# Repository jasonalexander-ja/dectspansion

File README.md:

# DECTspansion 

A DECT module for your EMFCamp Tildagon badge. 

Requires a headphone input. 

Based on [sc14cvmdect-devboard](https://github.com/funkeleinhorn/sc14cvmdect-devboard) by [funkeleinhorn](https://github.com/funkeleinhorn) and [EMFCamp](https://www.emfcamp.org/) [hexpansion](https://github.com/emfcamp/badge-2024-hardware/tree/main/hexpansion). 

Currently in early prototype stage. 

## Components 

| Component | Value          | Footprint      |
|-----------|----------------|----------------|
| C1        | 47pF           | 0603           |
| C2        | 2.2uF          | 0805           |
| C3        | 10uF           | 0805           |
| C4        | 2.2uF          | 0805           |
| C5        | 100nF          | 0603           |
| C6        | 1nF            | 0603           |
| C7        | 47pF           | 0603           |
| D1        | OSK40603C1E    | 0603           |
| D2        | ORH-B36G       | 0603           |
| J2        | 1x3 Pin header | 2.54mm         |
| J3        | SJ-4351X       | SMT audio jack |
| J4        | 1x2 Pin header | 2.54mm         |
| R1        | 1K             | 0603           |
| R2        | 470R           | 0603           |
| R3        | 470R           | 0603           |
| R4        | 1K             | 0603           |
| R5        | 1K             | 0603           |
| R6        | 1K             | 0603           |
| U1        | SC14VCMDECT    |                |
| U2        | 74AVC4T3144    | XQFN12         |
| U3        | ZD24C64A       | TSSOP-8        |
| LS1       | CMT-322-65     |                |

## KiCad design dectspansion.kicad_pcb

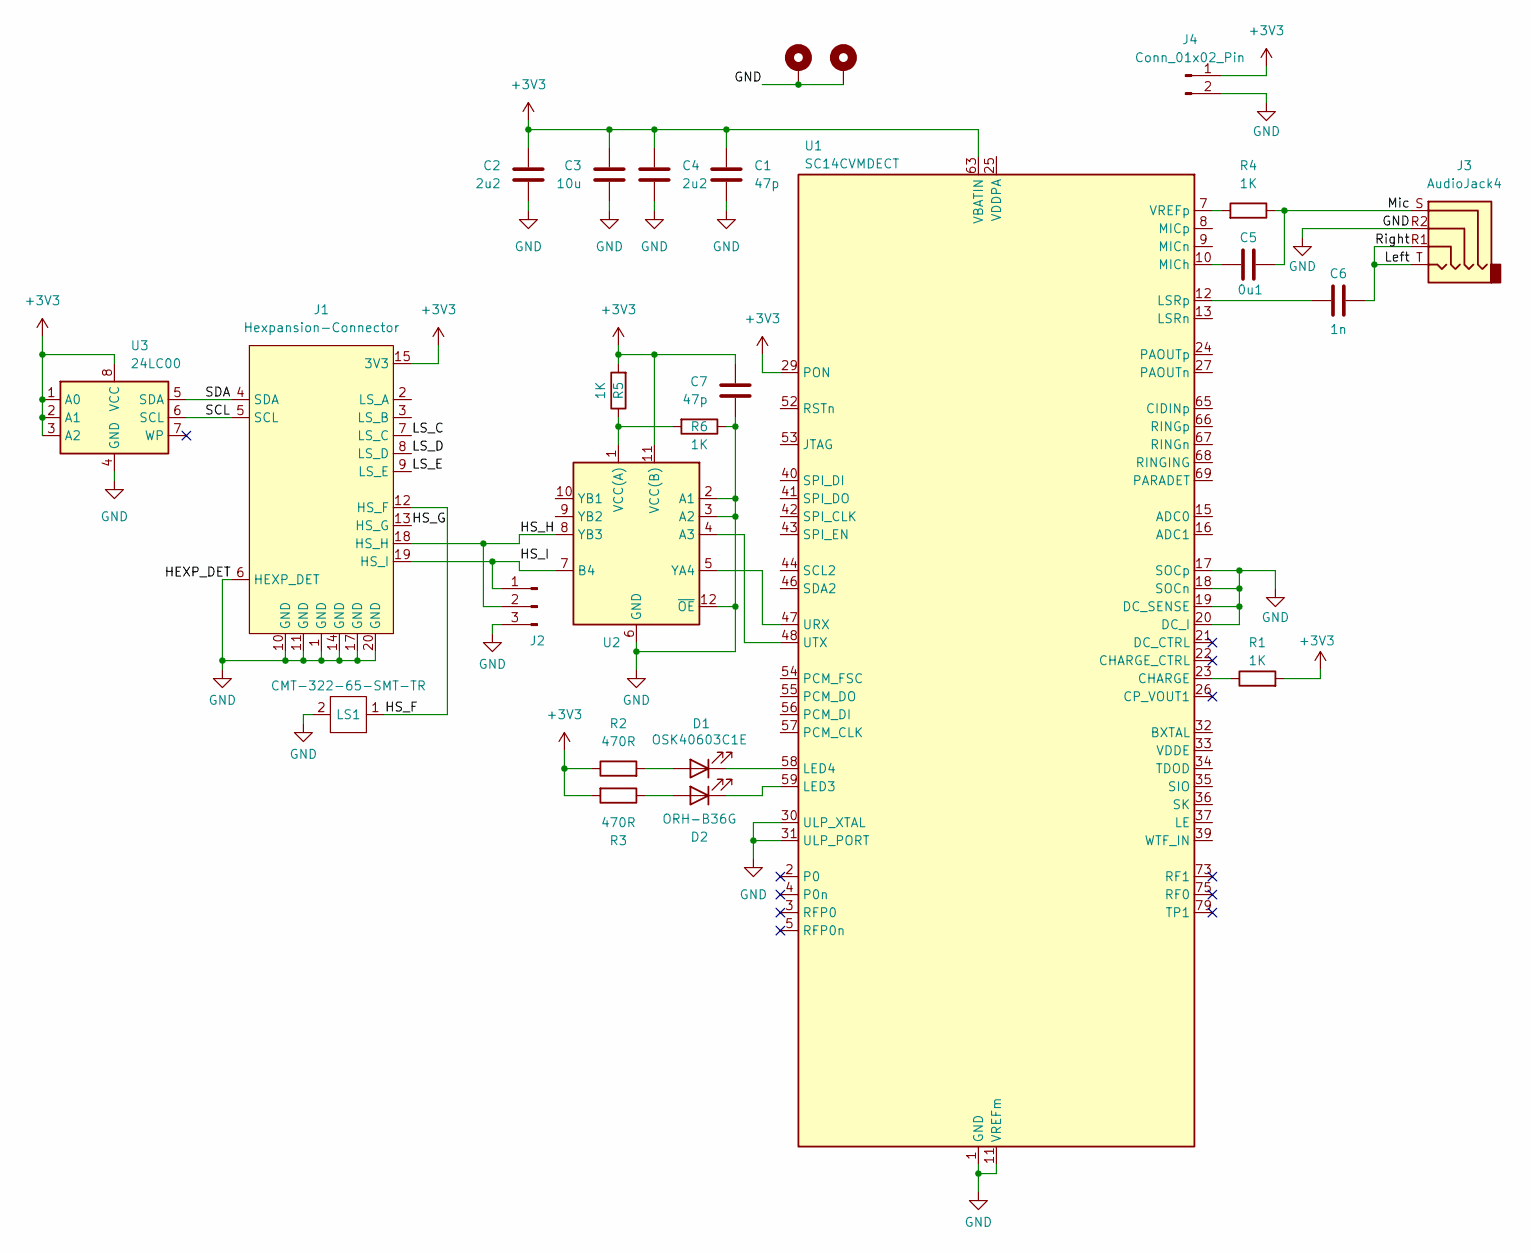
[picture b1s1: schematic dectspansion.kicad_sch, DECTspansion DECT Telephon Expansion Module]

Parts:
C1, C7: 47p; C_0603_1608Metric
C2, C4: 2u2; C_0805_2012Metric
C3: 10u; C_0805_2012Metric
C5: 0u1; C_0603_1608Metric
C6: 1n; C_0603_1608Metric
D1: OSK40603C1E; LED_0603_1608Metric
D2: ORH-B36G; LED_0603_1608Metric
H1, H2: MountingHole_Pad; MountingHole_2.2mm_M2_Pad_Via
J1: Hexpansion-Connector; hexpansion-edge-connector
J2: Conn_01x03_Pin; PinHeader_1x03_P2.54mm_Vertical
J3: AudioJack4; Jack_3.5mm_CUI_SJ-4351X-SMT_Horizontal
J4: Conn_01x02_Pin; PinHeader_1x02_P2.54mm_Vertical
LS1: CMT-322-65-SMT-TR
R1, R4, R5, R6: 1K; R_0603_1608Metric
R2, R3: 470R; R_0603_1608Metric
U1: SC14CVMDECT
U2: 74AVC4T3144
U3: 24LC00; TSSOP-8_4.4x3mm_P0.65mm

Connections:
+3V3: C1.1, C2.1, C3.1, C4.1, C7.1, J1.15 (3V3), J1.16 (3V3), J4.1, R1.2, R2.1, R3.2, R5.2, U1.29 (PON), U1.63 (VBATIN), U1.64 (VBATIN), U2.11 (VCC(B)), U3.1 (A0), U3.2 (A1), U3.3 (A2), U3.8 (VCC)
/HS_F: J1.12 (HS_F), LS1.1
/HS_G: J1.13 (HS_G)
/HS_H: J1.18 (HS_H), J2.2, U2.8 (YB3)
/HS_I: J1.19 (HS_I), J2.1, U2.7 (B4)
/LS_C: J1.7 (LS_C)
/LS_D: J1.8 (LS_D)
/LS_E: J1.9 (LS_E)
/Left: C6.1, J3.R1, J3.T
/Mic: C5.2, J3.S, R4.1
/SCL: J1.5 (SCL), U3.6 (SCL)
/SDA: J1.4 (SDA), U3.5 (SDA)
GND: C1.2, C2.2, C3.2, C4.2, C7.2, H1.1, H2.1, J1.1 (GND), J1.6 (HEXP_DET), J1.10 (GND), J1.11 (GND), J1.14 (GND), J1.17 (GND), J1.20 (GND), J2.3, J3.R2, J4.2, LS1.2, R6.1, U1.1 (GND), U1.6 (GND), U1.11 (VREFm), U1.14 (GND), U1.17 (SOCp), U1.18 (SOCn), U1.19 (DC_SENSE), U1.20 (DC_I), U1.28 (GND), U1.30 (ULP_XTAL), U1.31 (ULP_PORT), U1.38 (GND), U1.45 (GND), U1.49 (GND), U1.50 (GND), U1.51 (GND), U1.60 (GND), U1.70 (GND), U1.71 (GND), U1.72 (GND), U1.74 (GND), U1.76 (GND), U1.77 (GND), U1.78 (GND), U1.80 (GND), U2.2 (A1), U2.3 (A2), U2.6 (GND), U2.12 (~OE), U3.4 (GND)
unnamed: D1.2 (A), R2.2
unnamed: D1.1 (K), U1.58 (LED4)
unnamed: D2.2 (A), R3.1
unnamed: D2.1 (K), U1.59 (LED3)
unnamed: R1.1, U1.23 (CHARGE)
unnamed: C6.2, U1.12 (LSRp)
unnamed: C5.1, U1.10 (MICh)
unnamed: U1.47 (URX), U2.5 (YA4)
unnamed: U1.48 (UTX), U2.4 (A3)
unnamed: R4.2, U1.7 (VREFp)
unnamed: R5.1, R6.2, U2.1 (VCC(A))

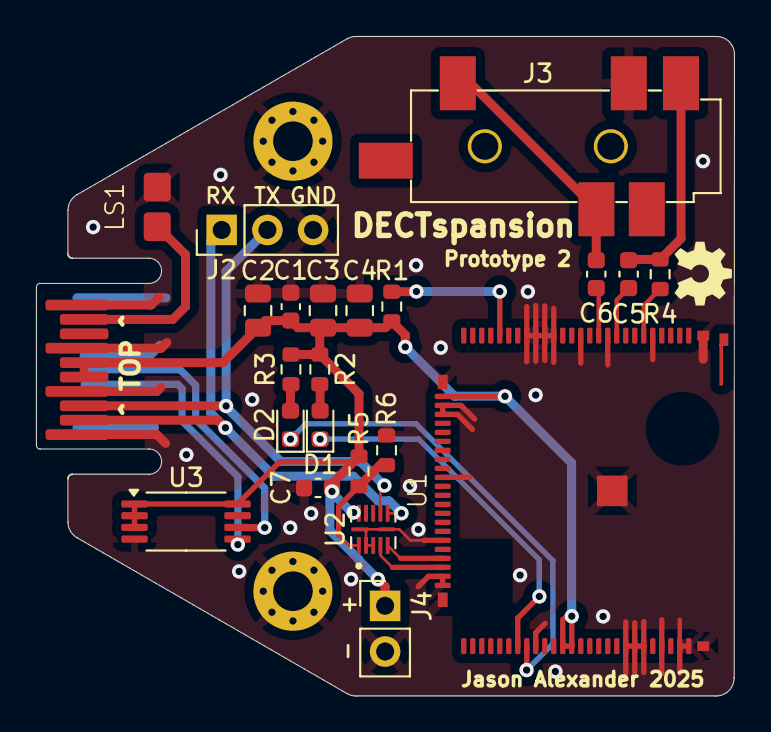
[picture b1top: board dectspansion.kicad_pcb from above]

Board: 4 copper layers, 38.8 x 36.6 mm, 25 parts (0 on the bottom side), 20 nets.

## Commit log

2025-07-21 Created PCB layout
2025-07-21 Adjustments to PCB layout
2025-07-21 Added gerbers
2025-07-22 Adjustments to schmatic, board layout, and added part list to readme
2025-07-22 Added gerbers to zip
2025-07-22 Added uart level shifting
2025-07-22 Added level shifitng, updated schematic, layout and gerbers
2025-07-23 Removed unused files
2025-07-23 Fixed bug
2025-07-23 Added eeprom to board, updated to prototype 2
2025-07-23 Removed eeprom capacitors, and solder jumper
2025-07-24 Added piezo ringer
2025-07-24 Added PDF schematic
2025-08-09 Added HTML bom

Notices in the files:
dectspansion.kicad_pcb:
https://cern-ohl.web.cern.ch
Licence: CERN Open Hardware Licence Version 2 - Strongly Reciprocal
